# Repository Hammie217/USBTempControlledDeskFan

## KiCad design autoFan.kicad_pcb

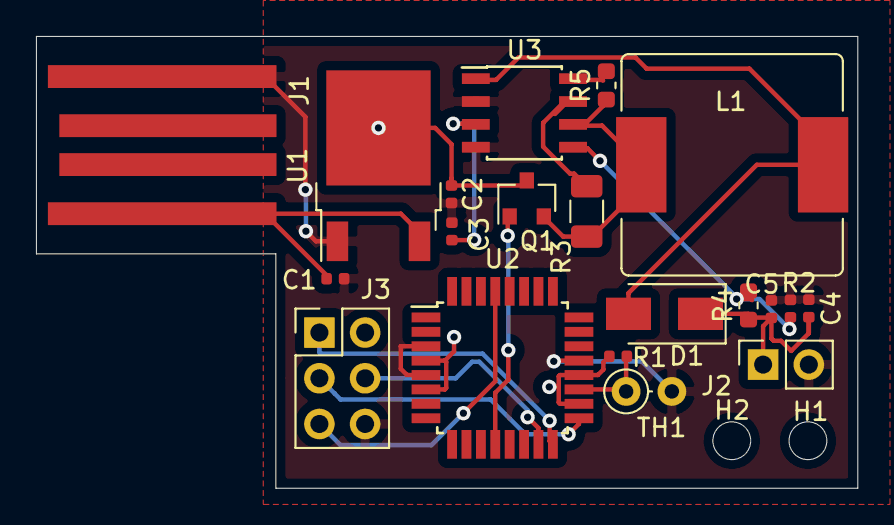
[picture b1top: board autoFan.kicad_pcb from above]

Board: 2 copper layers, 45.6 x 25.1 mm, 22 parts (0 on the bottom side), 16 nets.

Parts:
C1, C2: 0.1u; C_0402_1005Metric
C3: 1.5n; C_0402_1005Metric
C4: 33p; C_0402_1005Metric
C5: 10p; C_0402_1005Metric
D1: D; D_SMA
H1: Strain+; MountingHole_2.1mm
H2: Strain-; MountingHole_2.1mm
J1: USB_A; USB_A_PCBEDGE
J2: Fan; PinSocket_1x02_P2.54mm_Vertical
J3: Conn_02x03_Odd_Even; PinHeader_2x03_P2.54mm_Vertical
L1: 170u; L_Bourns_SRR1210A
Q1: AO3400A; SOT-23
R1: 100k; R_0402_1005Metric
R2: 1.5k; R_0402_1005Metric
R3: 0.1; R_1206_3216Metric
R4: 13k; R_0603_1608Metric
R5: 82; R_0603_1608Metric
TH1: 100k; L_Axial_L5.3mm_D2.2mm_P2.54mm_Vertical_Vishay_IM-1
U1: LM317_3PinPackage; TO-252-2
U2: ATmega328P-AU; TQFP-32_7x7mm_P0.8mm
U3: MC34063AD; SOIC-8_3.9x4.9mm_P1.27mm

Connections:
5V: C2.1, J3.2, Q1.3, R1.1, U1.2, U2.4, U2.6, U2.18, U2.20
GND: C1.2, C2.2, C3.2, C4.2, C5.2, J1.4, J2.2, J3.6, R2.2, TH1.2, U1.1, U2.3, U2.5, U2.21, U3.2, U3.4
MISO: J3.1, U2.16
MOSI: J3.4, U2.15
unnamed: C1.1, J1.1, U1.3
unnamed: C3.1, U3.3
unnamed: C4.1, C5.1, D1.1, J2.1, R4.1
unnamed: D1.2, L1.2, U3.1
unnamed: L1.1, Q1.2, R3.1, R5.1, U3.6
unnamed: Q1.1, U2.12
unnamed: R1.2, TH1.1, U2.19
unnamed: R2.1, R4.2, U3.5
unnamed: R3.2, U3.7
unnamed: R5.2, U3.8
RESET: J3.5, U2.29
SCK: J3.3, U2.17

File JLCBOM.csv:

Comment,Designator,Footprint,,
100nF,"C1,C2",0402_C,,
1.5nF,C3,0402_C,,
33pF,C4,0402_C,,
10p,C5,0402_C,,
D,D1,SMA_D,,
AO3400A,Q1,SOT-23,,
100kR,R1,0402_R,,
1.5kR,R2,0402_R,,
0.1R,R3,1206_R,,
13kR,R4,0603_R,,
82R,R5,0603_R,,
LM317,U1,TO-252-2,,
ATmega328P-AU,U2,TQFP-32_7x7mm_P0.8mm,,
MC34063AD,U3,SOIC-8_3.9x4.9mm_P1.27mm,,
,,,,
